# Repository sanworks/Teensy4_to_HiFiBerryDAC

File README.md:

# Teensy4_to_HiFiBerryDAC
Breakout boards to interface PJRC Teensy 4.X with HiFiBerry DAC boards

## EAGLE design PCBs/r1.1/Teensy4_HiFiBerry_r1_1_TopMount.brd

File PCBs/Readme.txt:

Notes about the Teensy4 HiFiBerry Breakout board

Version 1.1 STRONGLY recommended!

There are two versions of the board:
1. rev 1.X-T mounts to the HiFiBerry DAC's male GPIO header from above, 
using adafruit part# 1979: https://www.adafruit.com/product/1979

2. rev 1.X-B mounts to the HiFiBerry DAC's female GPIO header from below, 
using adafruit part# 3662: https://www.adafruit.com/product/3662

Other components are:
C1: 0.01uf ceramic cap, 0805 size, Yageo MPN# CC0805KRX7R9BB103 or equivalent 
C2: 0.1uf ceramic cap, 0805 size,  Taio Yuden MPN# UMK212B7104KG-T or equivalent   
C3: 4.7uf ceramic cap, 1206 size, Kemet MPN# C1206C475K5RACTU or equivalent
FB1: Ferrite bead, 0603 size, Taio Yuden MPN# FBTH1608HL300-T or equivalent 

Ordering:
The boards can be ordered from OSHPark, here:
rev 1.X-T: https://oshpark.com/shared_projects/HEg1rLr4
rev 1.X-B: https://oshpark.com/shared_projects/9LjQGttw

Notes: Both boards can be used with either Teensy 4.0 or 4.1.
       In rev 1.X-T, a tall pin header is used to clear the RCA jacks, increasing total height
       Three-pin header holes are available for mechanical support at the end of T4.1 (optional)
       In rev 1.X-B, HiFiBerry will block the top of the Teensy board (reset button, etc).

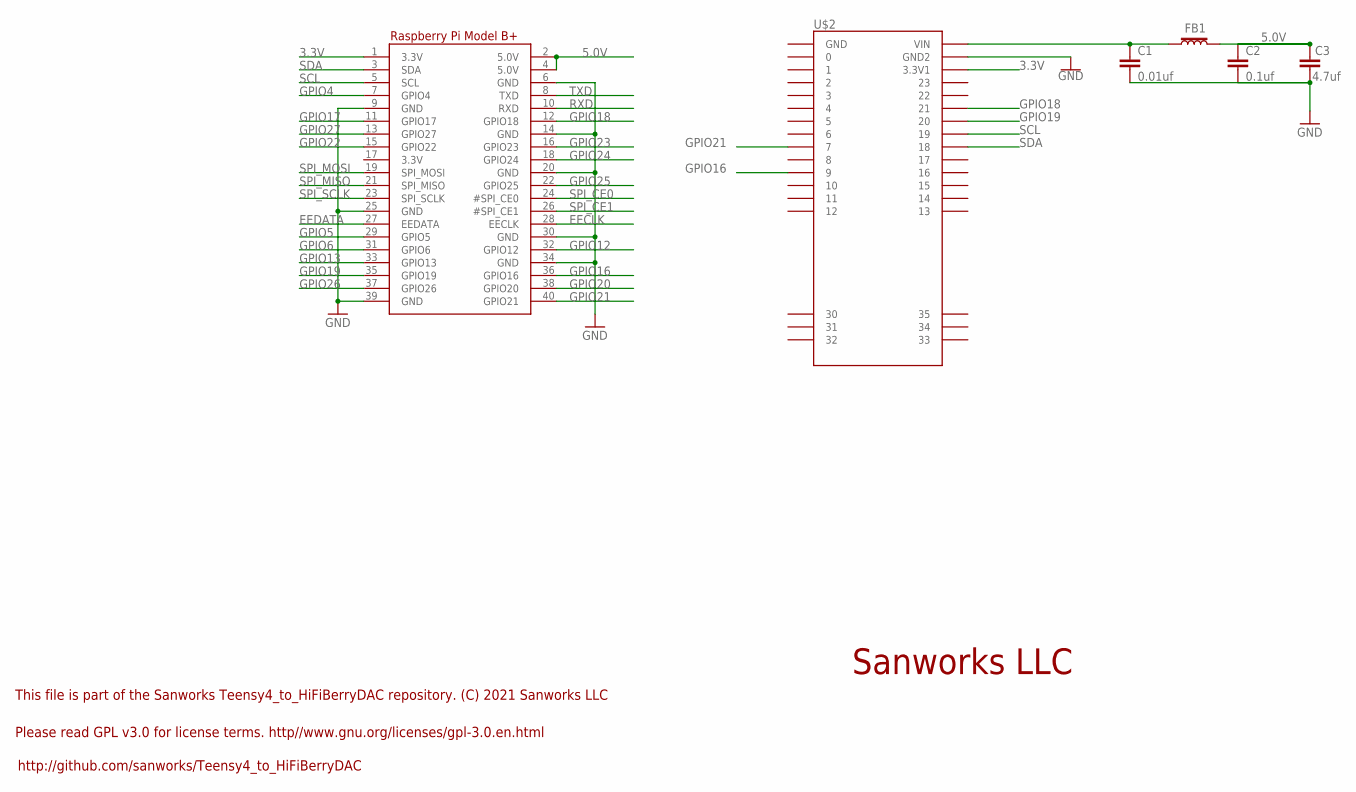
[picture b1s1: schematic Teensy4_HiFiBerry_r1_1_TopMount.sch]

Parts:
C1: 0.01uf; 0805
C2: 0.1uf; 0805
C3: 4.7uf; 1206@2
FB1: FERRITE_BEAD-0603; 0603
RPI1: RASPBERRYPI_BPLUS_IDC; 2X20
U$2: TEENSY4-4.1_FORAUDIO

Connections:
3.3V: RPI1.1 (3.3V), U$2.3V3_LO (3.3V1)
5.0V: C2.1, C3.2, FB1.2, RPI1.2 (5.0V), RPI1.4 (5.0V)
EECLK: RPI1.28 (EECLK)
EEDATA: RPI1.27 (EEDATA)
GND: C1.2, C2.2, C3.1, RPI1.6 (GND), RPI1.9 (GND), RPI1.14 (GND), RPI1.20 (GND), RPI1.25 (GND), RPI1.30 (GND), RPI1.34 (GND), RPI1.39 (GND), U$2.GND (GND2)
GPIO4: RPI1.7 (GPIO4)
GPIO5: RPI1.29 (GPIO5)
GPIO6: RPI1.31 (GPIO6)
GPIO12: RPI1.32 (GPIO12)
GPIO13: RPI1.33 (GPIO13)
GPIO16: RPI1.36 (GPIO16), U$2.9
GPIO17: RPI1.11 (GPIO17)
GPIO18: RPI1.12 (GPIO18), U$2.21/A7 (21)
GPIO19: RPI1.35 (GPIO19), U$2.20/A6 (20)
GPIO20: RPI1.38 (GPIO20)
GPIO21: RPI1.40 (GPIO21), U$2.7
GPIO22: RPI1.15 (GPIO22)
GPIO23: RPI1.16 (GPIO23)
GPIO24: RPI1.18 (GPIO24)
GPIO25: RPI1.22 (GPIO25)
GPIO26: RPI1.37 (GPIO26)
GPIO27: RPI1.13 (GPIO27)
RXD: RPI1.10 (RXD)
SCL: RPI1.5 (SCL), U$2.19/A5/SCL (19)
SDA: RPI1.3 (SDA), U$2.18/A4/SDA (18)
SPI_CE0: RPI1.24 (#SPI_CE0)
SPI_CE1: RPI1.26 (#SPI_CE1)
SPI_MISO: RPI1.21 (SPI_MISO)
SPI_MOSI: RPI1.19 (SPI_MOSI)
SPI_SCLK: RPI1.23 (SPI_SCLK)
TXD: RPI1.8 (TXD)
VUSB: C1.1, FB1.1, U$2.VIN

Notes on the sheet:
http://github.com/sanworks/Teensy4_to_HiFiBerryDAC
Please read GPL v3.0 for license terms. http//www.gnu.org/licenses/gpl-3.0.en.html
This file is part of the Sanworks Teensy4_to_HiFiBerryDAC repository. (C) 2021 Sanworks LLC
Sanworks LLC

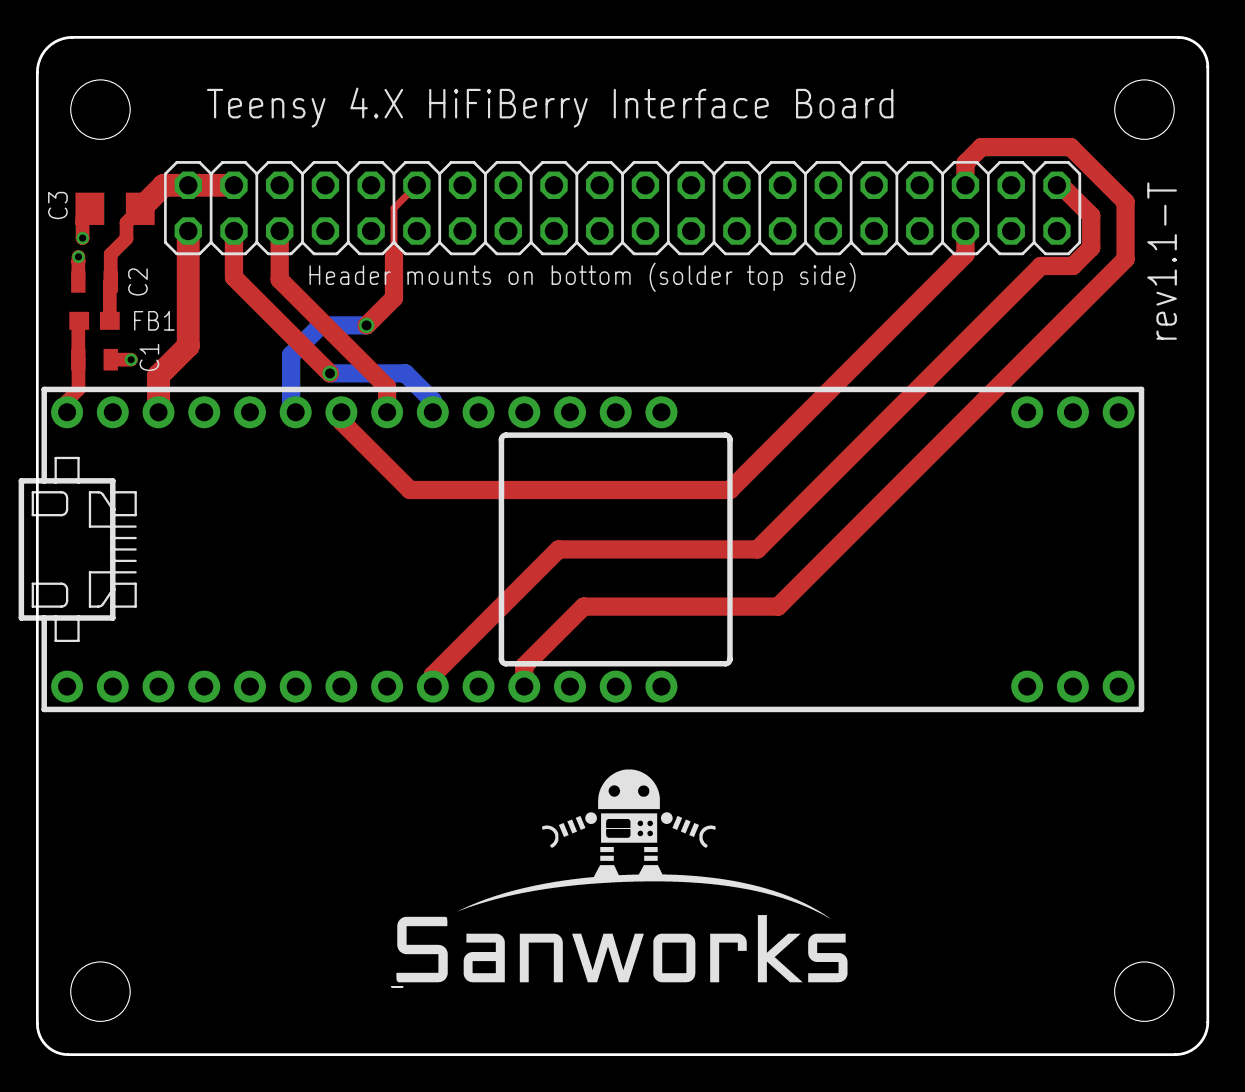
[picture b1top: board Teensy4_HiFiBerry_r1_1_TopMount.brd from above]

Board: 2 copper layers, 65.0 x 56.5 mm, 7 parts (0 on the bottom side), 10 nets.

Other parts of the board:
U$1: SANWORKS_LOGO

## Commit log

2021-02-09 -Fixed bit clock divider. I2S master mode now plays audio at the correct sampling rate
2021-02-17 -Added support for DAC2 Pro -Reconfigured device selection macros
2021-02-17 -Updated firmware notes -Removed alpha-test advisory
2021-02-20 -Changed default audio memory to accomodate more applications -Changed sine sweep range to match human hearing range -Added warning about performance issue with top-mount version of the PCB
2021-02-20 -Added Frequency sweep example for DAC2 HD using 192kHz sampling
2021-02-25 -Added example sketches to configure board in USB passthrough mode (i.e. to make it act as a USB sound card for the PC) for DAC2 Pro and DAC2 HD
2021-02-28 -Updated notes to reflect that top-mount board issue specifically affects DAC2 HD
2021-07-11 -Updated PCB design to v1.1. The new design adds USB power filtering. This fixes the DAC2 HD stability issue with v1.0

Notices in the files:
parts and their libraries:
microbuilder: This work is placed in the public domain, and may be freely used for commercial and non-commercial work with the following conditions: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
SparkFun-Capacitors: Licensing: Creative Commons ShareAlike 4.0 International - https://creativecommons.org/licenses/by-sa/4.0
